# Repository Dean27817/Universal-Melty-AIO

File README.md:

# Universal-Melty-AIO
A repository of code and hardware files for a universal melty board that uses two accelerometers to make a PCB that should be able to work in any meltybrain battlebot.

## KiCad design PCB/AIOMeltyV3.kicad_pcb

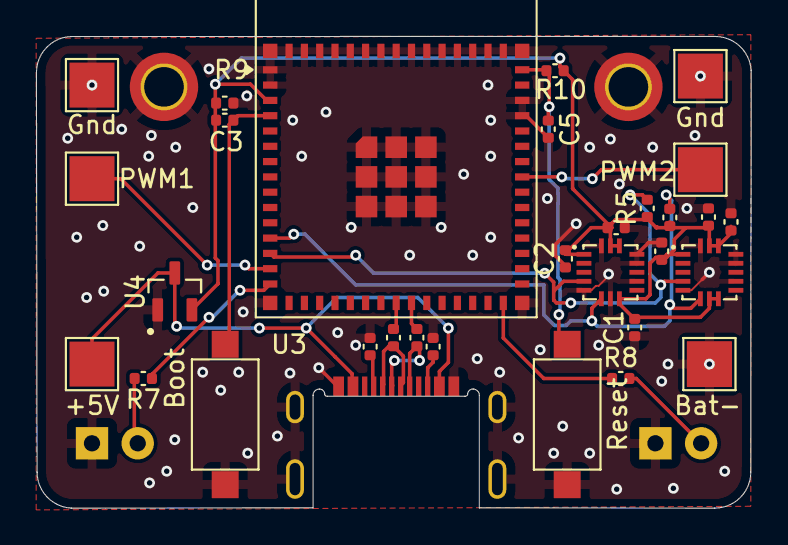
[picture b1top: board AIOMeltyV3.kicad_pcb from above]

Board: 2 copper layers, 39.7 x 26.2 mm, 33 parts (0 on the bottom side), 17 nets.

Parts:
C1, C1#2, C2, C3, C4, C5, C12, C13: 100nf; C_0402_1005Metric
D1, D2: CQY99; LED_D5.0mm_IRGrey
H1: PWM1; TestPoint_Pad_2.5x2.5mm
H2: PWM2; TestPoint_Pad_2.5x2.5mm
H3: Bat-; TestPoint_Pad_2.5x2.5mm
H3#2, H3#3: Gnd; TestPoint_Pad_2.5x2.5mm
H4: +5V; TestPoint_Pad_2.5x2.5mm
J1: USB4500-03-0-A_REVA1; GCT_USB4500-03-0-A_REVA1
R1, R2: 27.4; C_0402_1005Metric
R3, R4: 5.1k; C_0402_1005Metric
R5, R6, R9, R10: 10k; C_0402_1005Metric
R7, R8: R; C_0402_1005Metric
SW1: Boot; SW_SPST_CK_RS282G05A3
SW2: Reset; SW_SPST_CK_RS282G05A3
U1, U2: QFN300X300X100-16N
U3: ESP32-S3-MINI-1; ESP32-S2-MINI-1
U4: RT9161A-33GV; 5-3.3V LDO

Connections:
+3V3: C1.2, C1#2.2, C2.2, C3.2, C4.1, C12.1, C13.1, R5.1, R6.1, R9.1, R10.1, U1.1 (VDD_IO), U1.8 (CS), U1.14 (VDD), U1.15 (VDD), U2.1 (VDD_IO), U2.7 (SDO), U2.8 (CS), U2.14 (VDD), U2.15 (VDD), U3.3 (3V3), U4.2 (VOUT)
+5V: J1.A4_B9 (VBUS_A), J1.B4_A9 (VBUS_B), U4.3 (VIN)
GND: C1.1, C1#2.1, C2.1, C3.1, C4.2, C5.1, C12.2, C13.2, D1.1 (K), D2.1 (K), H3.1, H3#2.1, H3#3.1, J1.A1_B12 (GND_A), J1.B1_A12 (GND_B), J1.SH1 (SHELL_GND), J1.SH2 (SHELL_GND), J1.SH3 (SHELL_GND), J1.SH4 (SHELL_GND), R3.2, R4.2, SW1.1, SW2.1, U1.5 (GND), U1.7 (SDO), U1.10 (GND), U1.12 (GND), U1.13 (GND), U1.16 (GND), U2.5 (GND), U2.10 (GND), U2.12 (GND), U2.13 (GND), U2.16 (GND), U3.1 (GND), U3.2 (GND), U3.42 (GND), U3.43 (GND), U3.46 (GND), U3.47 (GND), U3.48 (GND), U3.49 (GND), U3.50 (GND), U3.51 (GND), U3.52 (GND), U3.53 (GND), U3.54 (GND), U3.55 (GND), U3.56 (GND), U3.57 (GND), U3.58 (GND), U3.59 (GND), U3.60 (GND), U3.61 (GND), U3.62 (GND), U3.63 (GND), U3.64 (GND), U3.65 (GND), U4.1 (GND)
Header: R8.1, U3.30 (IO48)
unnamed: D1.2 (A), R7.2
unnamed: D2.2 (A), R8.2
unnamed: J1.A5 (CC1), R4.1
unnamed: J1.B5 (CC2), R3.1
unnamed: C5.2, R10.2, SW2.2, U3.45 (EN)
unnamed: R9.2, SW1.2, U3.4 (IO0)
Power: R7.1, U3.15 (IO11)
SCL: R5.2, U1.4 (SCL), U2.4 (SCL), U3.13 (IO9)
SDA: R6.2, U1.6 (SDA), U2.6 (SDA), U3.12 (IO8)
USB1_N: J1.A7 (DN1), J1.B7 (DN2), R1.1
USB1_P: J1.A6 (DP1), J1.B6 (DP2), R2.2
USB_N: R1.2, U3.23 (USB_D-)
USB_P: R2.1, U3.24 (USB_D+)

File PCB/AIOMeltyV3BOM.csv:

Reference,Value,Footprint,Qty
"C1,C2,C3,C4,C5,C13",100nf,-- mixed values --,6
"D1,D2",CQY99,LED_THT:LED_D5.0mm_IRGrey,2
J1,USB4500-03-0-A_REVA1,USB4500-03-0-A_REVA1:GCT_USB4500-03-0-A_REVA1,1
"R1,R2",27.4,Capacitor_SMD:C_01005_0402Metric,2
"R3,R4",5.1k,Capacitor_SMD:C_01005_0402Metric,2
"R5,R6,R9,R10",10k,Capacitor_SMD:C_01005_0402Metric,4
SW1,Boot,Button_Switch_SMD:SW_SPST_CK_RS282G05A3,1
SW2,Reset,Button_Switch_SMD:SW_SPST_CK_RS282G05A3,1
"U1,U2",~,USB4500-03-0-A_REVA1:QFN300X300X100-16N,2
U3,ESP32-S3-MINI-1,RF_Module:ESP32-S2-MINI-1,1
U4,RT9161A-33GV,USB4500-03-0-A_REVA1:5-3.3V LDO,1

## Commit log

2025-06-05 Added PCB flies
    I have had the PCB done for a bit and am now uploading all the files
2025-06-05 Added old code files
    This is the code from a previous Meltybrain, HDD. It only works with one accelerometer and is currently a mess. This will be changed, but it is good to have here as a backup.
2025-07-17 added makefile
2025-07-26 changed code over to work with the new PCB
2025-07-27 some things work. I think there may be hardware issues
2025-07-27 updated PCB
2025-07-29 Robot moves, I2C should now be on the correct pins
2025-07-29 Remade most of the GetAngle.h
2025-07-29 I think I finally fixed the kinimatics
2025-08-06 updated PCB I2C
2025-08-06 changed Code folder to code to make life easy
2025-08-13 changed wifi code. No longer need to connect at startup
2025-08-15 added safety to last code
2025-09-06 code was not up to date
2025-09-13 saving before gpts refactor
2025-09-13 refacter to -1 to 1
2025-10-06 push before switching to ELRS
2026-01-09 coppied code from working repo (HDD)
2026-01-09 I belive this is PIO updating librarys
2026-01-09 added configs
2026-01-09 changed constants and to a two accel system
